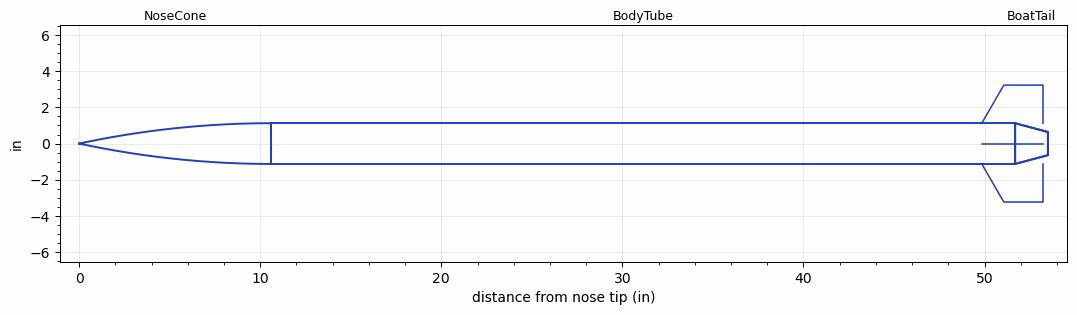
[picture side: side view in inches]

<RASAeroDocument>
 <FileVersion>2</FileVersion>
 <RocketDesign>
  <NoseCone>
   <Length>10.6</Length>
   <Diameter>2.25</Diameter>
   <Shape>Tangent Ogive</Shape>
   <BluntRadius>0.062</BluntRadius>
   <Location>0</Location>
  </NoseCone>
  <BodyTube>
   <Length>41.09</Length>
   <Diameter>2.25</Diameter>
   <Location>10.6</Location>
   <BoattailLength>1.81</BoattailLength>
   <BoattailRearDiameter>1.28</BoattailRearDiameter>
   <Overhang>1.54</Overhang>
   <Fin>
    <Count>4</Count>
    <Chord>3.38</Chord>
    <Span>2.103</Span>
    <SweepDistance>1.215</SweepDistance>
    <TipChord>2.165</TipChord>
    <Thickness>0.123</Thickness>
    <Location>1.84</Location>
    <AirfoilSection>Double Wedge</AirfoilSection>
    <FX1>1.4863</FX1>
    <FX3>0.465</FX3>
   </Fin>
   <Protuberance>
    <StreamlinedNoBaseDrag>0</StreamlinedNoBaseDrag>
    <StreamlinedWithBaseDrag>0.178</StreamlinedWithBaseDrag>
    <InclinedPlate1Angle>0</InclinedPlate1Angle>
    <InclinedPlate1FrontalArea>0</InclinedPlate1FrontalArea>
    <InclinedPlate2Angle>0</InclinedPlate2Angle>
    <InclinedPlate2FrontalArea>0</InclinedPlate2FrontalArea>
   </Protuberance>
  </BodyTube>
  <BoatTail>
   <Length>1.81</Length>
   <Diameter>2.25</Diameter>
   <RearDiameter>1.28</RearDiameter>
   <Location>51.69</Location>
  </BoatTail>
  <Surface>Smooth (Zero Roughness)</Surface>
  <ModifiedBarrowman>True</ModifiedBarrowman>
  <Turbulence>False</Turbulence>
  <SustainerNozzle>1.25</SustainerNozzle>
  <UseBooster1>False</UseBooster1>
  <UseBooster2>False</UseBooster2>
 </RocketDesign>
 <LaunchSite>
  <Altitude>3933</Altitude>
  <Pressure>0</Pressure>
  <RodAngle>0</RodAngle>
  <RodLength>12</RodLength>
  <Temperature>80</Temperature>
  <WindSpeed>0</WindSpeed>
 </LaunchSite>
 <Recovery>
  <Altitude1>1000</Altitude1>
  <Altitude2>1000</Altitude2>
  <DeviceType1>None</DeviceType1>
  <DeviceType2>None</DeviceType2>
  <Event1>False</Event1>
  <Event2>False</Event2>
  <Size1>1</Size1>
  <Size2>1</Size2>
  <EventType1>None</EventType1>
  <EventType2>None</EventType2>
  <CD1>1.33</CD1>
  <CD2>1.33</CD2>
 </Recovery>
 <MachAlt>
  <Item>0, 0</Item>
  <Item>0.42, 1</Item>
  <Item>0.9, 25000</Item>
  <Item>1.05, 30500</Item>
  <Item>1.2, 33000</Item>
  <Item>1.5, 37000</Item>
  <Item>2, 44000</Item>
  <Item>4, 59000</Item>
  <Item>5, 63000</Item>
  <Item>25, 122500</Item>
  <Item>0, 0</Item>
  <Item>0.42, 1</Item>
  <Item>0.9, 25000</Item>
  <Item>1.05, 30500</Item>
  <Item>1.2, 33000</Item>
  <Item>1.5, 37000</Item>
  <Item>2, 44000</Item>
  <Item>4, 59000</Item>
  <Item>5, 63000</Item>
  <Item>25, 122500</Item>
  <Item>0, 0</Item>
  <Item>0.42, 1</Item>
  <Item>0.9, 25000</Item>
  <Item>1.05, 30500</Item>
  <Item>1.2, 33000</Item>
  <Item>1.5, 37000</Item>
  <Item>2, 44000</Item>
  <Item>4, 59000</Item>
  <Item>5, 63000</Item>
  <Item>25, 122500</Item>
  <Item>0, 0</Item>
  <Item>0.42, 1</Item>
  <Item>0.9, 25000</Item>
  <Item>1.05, 30500</Item>
  <Item>1.2, 33000</Item>
  <Item>1.5, 37000</Item>
  <Item>2, 44000</Item>
  <Item>4, 59000</Item>
  <Item>5, 63000</Item>
  <Item>25, 122500</Item>
  <Item>0, 0</Item>
  <Item>0.42, 1</Item>
  <Item>0.9, 25000</Item>
  <Item>1.05, 30500</Item>
  <Item>1.2, 33000</Item>
  <Item>1.5, 37000</Item>
  <Item>2, 44000</Item>
  <Item>4, 59000</Item>
  <Item>5, 63000</Item>
  <Item>25, 122500</Item>
  <Item>0, 0</Item>
  <Item>0.42, 1</Item>
  <Item>0.9, 25000</Item>
  <Item>1.05, 30500</Item>
  <Item>1.2, 33000</Item>
  <Item>1.5, 37000</Item>
  <Item>2, 44000</Item>
  <Item>4, 59000</Item>
  <Item>5, 63000</Item>
  <Item>25, 122500</Item>
 </MachAlt>
 <SimulationList>
  <Simulation>
   <SustainerLaunchWt>0</SustainerLaunchWt>
   <SustainerNozzleDiameter>1.25</SustainerNozzleDiameter>
   <SustainerCG>37.42</SustainerCG>
   <SustainerIgnitionDelay>0</SustainerIgnitionDelay>
   <Booster1SeparationDelay>0</Booster1SeparationDelay>
   <Booster1IgnitionDelay>0</Booster1IgnitionDelay>
   <IncludeBooster1>False</IncludeBooster1>
   <Booster2Delay>0</Booster2Delay>
   <IncludeBooster2>False</IncludeBooster2>
  </Simulation>
 </SimulationList>
</RASAeroDocument>
